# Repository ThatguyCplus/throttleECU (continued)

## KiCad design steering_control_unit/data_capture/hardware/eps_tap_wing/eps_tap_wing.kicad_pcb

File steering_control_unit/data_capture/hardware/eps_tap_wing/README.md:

# EPS tap FeatherWing

A factory-assembled FeatherWing that holds the logger's whole front end, so the build has no loose resistors. It replaces the FeatherWing Proto and every part in section 3 of [BOM.md](../../BOM.md). The circuit is the same apart from the changes listed below.

**Rev 1.5: cheaper to build at JLCPCB**
- Divider values were re-picked from JLCPCB's **Basic** library, which loads with no setup fee; each Extended part type costs about $3. Extended types dropped from 8 to 2: the op-amp and the ADS1115.

  | Channel | Was | Now | Effect |
  |---|---|---|---|
  | VT3, VT6, VCC2 | 1M / 1.8M | 1M / 1M | 5 V → 2.50 V (was 3.21 V); resolution still ~0.016 %/step |
  | +B, X1–X4 | 1M / 150k | 1M / 100k | 36 V full scale (was 25 V); ~9 mV/step |
  | NEP, WLP, RT+, IG1 | 100k / 27k | 100k / 33k | 14.4 V → 3.57 V; still reads high at 9 V |
  | VSP | 100k / 180k | 100k / 100k | 5 V → 2.50 V |
  | Current, Vref | 10k / 18k | 10k / 47k | More of the ADC range used: better resolution |
  | Clamp diodes | BAT54WS | 1N4148WS | Basic part, lower leakage |
  | Op-amps | MCP6024 | MCP6004 | Same pins; about 1/10 the price |
- The BOM now carries a **JLCPCB Part #** column, so the upload matches exactly. The MCP6004 has no part number yet: pick MCP6004-I/ST at upload.
- `firmware/eps_logger/config.h` has a new `CFG_FRONT_END_TAP_WING` switch that sets the divider constants: 1 for this board, 0 for the hand-built Proto Wing.

**Rev 1.4: status LED, 4-layer board**
- **Red status LED** (D6, with R32 1 kΩ) on the **back**, next to the "LED" label. It's wired to Feather pin D13, which the logger firmware already uses for its status codes (`CFG_PIN_LED`), so it mirrors them with no firmware change. The two parts are 0805 so you can hand-solder them; or ask JLC for bottom-side assembly of just those two.
- **Now a 4-layer board.** With rev 1.3's extra parts plus the LED, the 2-layer board was full: the router always left one or two connections. With an inner GND plane and a third routing layer it routes completely, and the signal traces got **thicker (0.3 mm)**.
- Solder jumpers use plain rectangular pads. The rounded custom pads were being exported to the auto-router on the wrong layer.

**Rev 1.3: room to grow**
- **Four spare protected inputs, X1–X4,** for future signals: motor M+/M−, Vcc1, ground shift, or anything else that's a voltage. Each has the same protection as +B: a 1 MΩ series resistor with a bypass jumper, a 100 kΩ divider (0–36 V full scale) and a 1 nF filter. A second quad op-amp (U2) buffers them into an **ADS1115 16-bit ADC** (U3) on I2C at address 0x48.
- **J2 is now a 15-way JST XA** (2.5 mm pitch, positive locking latch). It's the same length as the old 11-way plug and carries the original 11 signals plus X1–X4.
- Passives went from 0603 to 0402 and the op-amps from SOIC-14 to TSSOP-14 to make room. Everything is still factory-assembled on one side.

**Rev 1.2:**
- All wiring is from the **back**: J2, J3 and the bypass jumpers are on the bottom side, and all 42 SMD parts moved to the top (still one-sided assembly).
- The wing is a "bottom Wing" (allowed by the Feather spec): it sits at the bottom of the stack, with the Feather plugged in on top.
- **HINDSIGHT** is on the back silkscreen, together with the terminal labels and "IGN OFF TO PLUG". The revision is on the top.

**Rev 1.1:**
- Follows the [Adafruit Feather specification](https://learn.adafruit.com/adafruit-feather/feather-specification).
- Each series resistor has a bypass solder jumper, so the probe resistors can live on the board or at the probe ends.
- Adds the current sensor's Vref channel on A5.
- The clamp terminal (J3) is now 4-way.

## Feather specification check

| Spec item | This wing |
|-----------|-----------|
| 0.9" × 2.0" board, 0.1" holes at each corner | 22.86 × 50.8 mm, four 2.5 mm holes 2.54 mm in from the edges |
| 16-pin strip on the bottom side, centred 1.0" from the left (USB) edge | Pins 1–16 at x = 6.35–44.45 mm (centre 25.4 mm), y = 21.59 mm |
| 12-pin strip on the top side, 1.2" from the left edge, 0.8" between strips | Pins 17–28 at x = 16.51–44.45 mm (centre 30.48 mm), y = 1.27 mm |
| Wings take 3.3 V from the Feather; at least 100 mA available | The op-amps and ADC draw about 2 mA from 3V3; the clamp draws ≤12 mA from USB |
| AREF, the free pin (right of TX), RX/TX, SPI and its CS: avoid | None of them are used |
| I2C pull-ups belong on Wings | The ADS1115 uses I2C; the Adalogger in the same stack already has the pull-ups |
| Reset button "ideally" on Wings | Not fitted: the OLED FeatherWing on top of the stack has one |
| Wings may be "bottom" Wings with the Feather on top | Used here, so the terminals face out of the back |

The board check script confirms the header pads line up with the Feather footprint every time the board is regenerated.

## Design rules

| Item | Value |
|------|-------|
| Layers | 4: **F.Cu** parts + signals, **In1.Cu** solid GND plane, **In2.Cu** signals + 3V3 + GND fill, **B.Cu** connectors + signals + GND fill |
| Signal traces | 0.3 mm. They carry microamps, so this is for robustness, not current |
| 3V3 / 5V traces | 0.3 mm. The 3V3 traces are short stubs and the USB 5 V carries ≤15 mA; 0.3 mm also fits into the 0.5 mm-pitch ADC pins |
| Status-LED traces | 0.2 mm (about 1.4 mA) |
| Clearance | 0.15 mm |
| Vias | 0.5 mm pad, 0.25 mm drill |

JLCPCB's standard minimum is 0.127 mm, so these widths have plenty of margin. A 4-layer board costs a little more than 2-layer, but it gives a solid ground plane under all the high-impedance inputs, which is better for noise. `make_pcb.py` still builds the 2-layer version if you set `EPS_LAYERS=2`, but with this many parts it won't fully route.

| File | What it is |
|------|------------|
| [eps_tap_wing.kicad_sch](eps_tap_wing.kicad_sch) / [schematic PDF](doc/eps_tap_wing_schematic.pdf) | Schematic. ERC: 0 errors, 0 warnings |
| [eps_tap_wing.kicad_pcb](eps_tap_wing.kicad_pcb) | Board, 50.8 × 22.86 mm (standard FeatherWing), 4 layers, fully routed. DRC: 0 errors, 0 unconnected, matches the schematic |
| [doc/render_top.png](doc/render_top.png), [doc/render_bottom.png](doc/render_bottom.png) | 3D renders |
| [fab/eps_tap_wing_bom_jlc.csv](fab/eps_tap_wing_bom_jlc.csv), [fab/eps_tap_wing_cpl_jlc.csv](fab/eps_tap_wing_cpl_jlc.csv) | Assembly BOM and pick-and-place, in JLCPCB's column format, SMD parts only |
| [gen/](gen/) | Generator scripts. The schematic and board are built from [gen/design.py](gen/design.py) |

## The stack

The tap wing also stacks with the [bench stim wing](../../../bench_stim_wing/README.md), which can power everything from 12 V and drive the EPS inputs. **When the stack runs from 12 V, its ground must go to the ECU end of A4 (PG)**, not chassis: see [STACK_MODES.md](../../STACK_MODES.md) for every combination.

```
  OLED FeatherWing
  Adalogger FeatherWing
  Feather M4 CAN          (its male headers plug down into the wing)
  ─ female headers soldered on the wing's top side ─
  EPS tap wing            (SMD on top, facing the Feather; ~8 mm of header gap is plenty)
  ─ back side: J2 taps, J3 clamp, bypass jumpers, labels ── wire from here
```

The terminals point out of the back of the stack, so the harness never has to pass between boards. Leave room under the stack for the J2 plug and its cable (about 15 mm).

Solder joints you make yourself: the two female header rows on the top (28 joints) and the two connectors on the back (19 joints). Every resistor, capacitor, diode, both op-amps and the ADC arrive already fitted. The status LED and its resistor (0805, on the back) are either 2 more hand-soldered parts or bottom-side assembly.

## Connectors

**J2, EPS taps** (JST XA B15B-XASK-1, 2.5 mm pitch, locking; mating housing XAP-15V-1 with SXA-001T-P0.6 crimp contacts, or buy pre-crimped XA leads). Read the back silkscreen with the board face down: the labels sit under each pin, and pin 1 (VT3) is at the right-hand end.

| J2 pin | Silk | Car pin | On the wing |
|--------|------|---------|-------------|
| 1 | VT3 | B10 | 1 MΩ / 1 MΩ → buffer → A2 |
| 2 | VT6 | B8 | 1 MΩ / 1 MΩ → buffer → A3 |
| 3 | VCC2 | B2 | 1 MΩ / 1 MΩ → buffer → A0 |
| 4 | GND | B9 (T/S GND) | 100 Ω → logger GND, the only ground reference |
| 5 | SHLD | cable shield | logger GND; don't connect the shield at the car end |
| 6 | +B | A2 | 1 MΩ / 100 kΩ → buffer → A1 |
| 7 | IG1 | B6 | 100 kΩ / 33 kΩ → D12 |
| 8 | RT+ | B11 | 100 kΩ / 33 kΩ → D11 (optional: leave it empty and it reads "off") |
| 9 | WLP | B13 | 100 kΩ / 33 kΩ → D9 |
| 10 | NEP | B14 | 100 kΩ / 33 kΩ → D6 |
| 11 | VSP | B4 | 100 kΩ / 100 kΩ → D5 |
| 12–15 | X1–X4 | spare | 1 MΩ / 100 kΩ → U2 buffer → ADS1115 AIN0–AIN3 |

The torque-sensor lines sit at one end, behind GND and SHLD, so a stray strand can't put +B onto them. +B's other neighbour is IG1, which is also battery level. The digital lines follow the Feather's pin order, so their tracks don't cross. Crimp every contact properly and check each wire with a tug.

**J3, current clamp** (Phoenix MPT 0,5/4-2,54 fixed screw terminal, 2.54 mm pitch). A 3.5 mm plug-in 4-way terminal would sit over the Feather-spec corner mounting holes. The clamp has its own flying leads anyway. Pin 1 is the one nearest the 16-pin header edge, marked with a triangle.

| J3 pin | HSTS016L wire |
|--------|---------------|
| 1 | red: +5 V (from the Feather USB pin, i.e. the power bank) |
| 2 | black: 0 V, plus the sensor cable's shield |
| 3 | yellow: OUT → 10 k / 47 k / 100 nF → A4 |
| 4 | white: Vref → 10 k / 47 k / 100 nF → A5 (current = Vout − Vref, which cancels the sensor's reference drift) |

## Probe resistors: on the board or at the probe

Each car-facing series resistor has a **solder jumper** across it. The jumpers are the row of pads under J2 on the back, one under each terminal, and they ship **open**.

| Where you want the resistors | What to do |
|------------------------------|------------|
| **On the board** (default) | Nothing. Leave the jumpers open. Protect the cable as described below |
| **At the probe ends** (whole cable protected, as in [PROTO_BUILD.md](../../PROTO_BUILD.md)) | Bridge each jumper with a blob of solder. Then fit 1 MΩ (VT3, VT6, VCC2, +B, X1–X4), 100 kΩ (VSP, NEP, WLP, RT+, IG1) and 100 Ω (GND) inline at the probes |

| Jumper | Bypasses | J2 terminal |
|--------|----------|-------------|
| JP1 | R3 (1 MΩ) | VT3 |
| JP2 | R5 (1 MΩ) | VT6 |
| JP3 | R1 (1 MΩ) | VCC2 |
| JP4 | R11 (100 Ω) | GND |
| JP5 | R7 (1 MΩ) | +B |
| JP6–JP10 | R20, R18, R16, R14, R12 (100 kΩ) | IG1, RT+, WLP, NEP, VSP |
| JP11–JP14 | R24, R26, R28, R30 (1 MΩ) | X1–X4 |

Never bridge a jumper without fitting its probe resistor: that connects the car straight to the dividers.

The pin map is the one `firmware/eps_logger/config.h` already uses, so the firmware needs no changes for the original signals.

## Spare inputs X1–X4

| Signal type | Change on the board |
|-------------|---------------------|
| Up to 36 V (battery-level, motor terminals) | None: 1 MΩ / 100 kΩ gives 0–3.27 V at the ADC |
| 0–5 V sensor | Swap the 100 kΩ (R25, R27, R29, R31) for 1 MΩ: 5 V → 2.50 V, same as VT3 |

The ADS1115 reads all four channels at about 200 samples per second each, with a programmable gain (±0.256 V to ±4.096 V). That suits slow-to-medium signals; anything that must line up sample-for-sample with torque belongs on the Feather's own ADC. The firmware doesn't read U3 yet.

## Safety: the one trade-off

With the probe resistors on the wing, the cable between the car and the wing is no longer behind them. A cable fault, such as a crushed jacket or a strand bridging two terminals, now reaches the EPS directly instead of through ≥100 kΩ. To make up for that:

- Use one sheathed multicore cable (12-core shielded, as in BOM.md §5). Strap it down so it can't chafe, and keep it away from the pedal box and seat rails.
- Crimp ferrules on every wire and heat-shrink each back-probe pin.
- Fit the plug and probes with the **ignition OFF** (this is printed on the board). Continuity-check neighbouring probes before key-on, as in BOM.md's worst-case table.
- Run the firmware's `c` lead check with the engine off, then running.

Faults on the logger side of the terminals are covered just as in BOM.md: everything after J2 is ≥100 kΩ (1 MΩ on the torque lines) from the car.

## Changes from the BOM.md front end

| BOM.md part | Wing part | Why |
|-------------|-----------|-----|
| MCP6024-I/P (DIP-14) | MCP6004-I/ST (TSSOP-14) | Same pinout and rail-to-rail, 1 pA inputs; 1 MHz instead of 10 MHz (plenty) for about a tenth of the price |
| BAT85 (DO-35) | 1N4148WS (SOD-323) | JLC Basic part, same 3V3 clamp role; 25 nA leakage can't disturb the dividers |
| 2 × 6-way screw terminal | 15-way locking JST XA + 4-way screw terminal | Unplug the car harness in one go; 4 spare positions |
| — | X1–X4 inputs, second quad op-amp, ADS1115 | Room for future signals |
| — | 10 k / 47 k / 100 nF on the clamp's Vref → A5 | Cancels the current sensor's reference drift (needs a firmware update to use, see below) |
| — | 14 bypass solder jumpers | Choose between probe resistors on the board or at the probes |

All resistors are 0402 1 % parts and all capacitors are 0402 X7R (JLC Basic).

## Rebuilding the design

All scripts run with KiCad 10's bundled Python, from `gen/`:

```bash
"/c/Program Files/KiCad/10.0/bin/python.exe" make_sch.py
"/c/Program Files/KiCad/10.0/bin/kicad-cli.exe" sch export netlist -o ../eps_tap_wing.net ../eps_tap_wing.kicad_sch
sh route.sh
```

`route.sh` runs four steps:
1. `make_pcb.py place` places the parts and exports a Specctra DSN.
2. Freerouting routes the board.
3. `make_pcb.py finish` imports the routes and pours GND on both layers.
4. DRC with schematic parity runs, then `export_fab.py` writes the Gerbers, drill files, BOM and CPL.

Change the circuit or the placement in `design.py` and re-run. Hand-editing in KiCad is also fine, but then stop running the generators, because they would overwrite your edits.

## What's left

1. **Gerbers are ready** in `fab/eps_tap_wing_gerbers.zip`, with the assembly BOM and CPL next to them. **Nothing has been ordered or published.**
2. Before ordering:
   - Check the JLC CPL rotations in their viewer. Bottom-side parts are where offsets usually need a tweak.
   - Match each MPN to an in-stock LCSC part.
3. **Firmware:** `eps_logger` doesn't read A5 or the ADS1115 yet.
   - To use the Vref channel, compute current as A4 − A5 instead of A4 minus the key-on zero.
   - Reading X1–X4 means polling U3 over I2C (0x48) a few hundred times a second.
   - Both need new fields in the log record.

Routing used Freerouting 2.2.0 on a downloaded Temurin JRE 25 (not installed system-wide). To re-route: `JAVA=<path to java 25> sh gen/route.sh`. Freerouting results vary from run to run, so re-run it if a connection is left over.

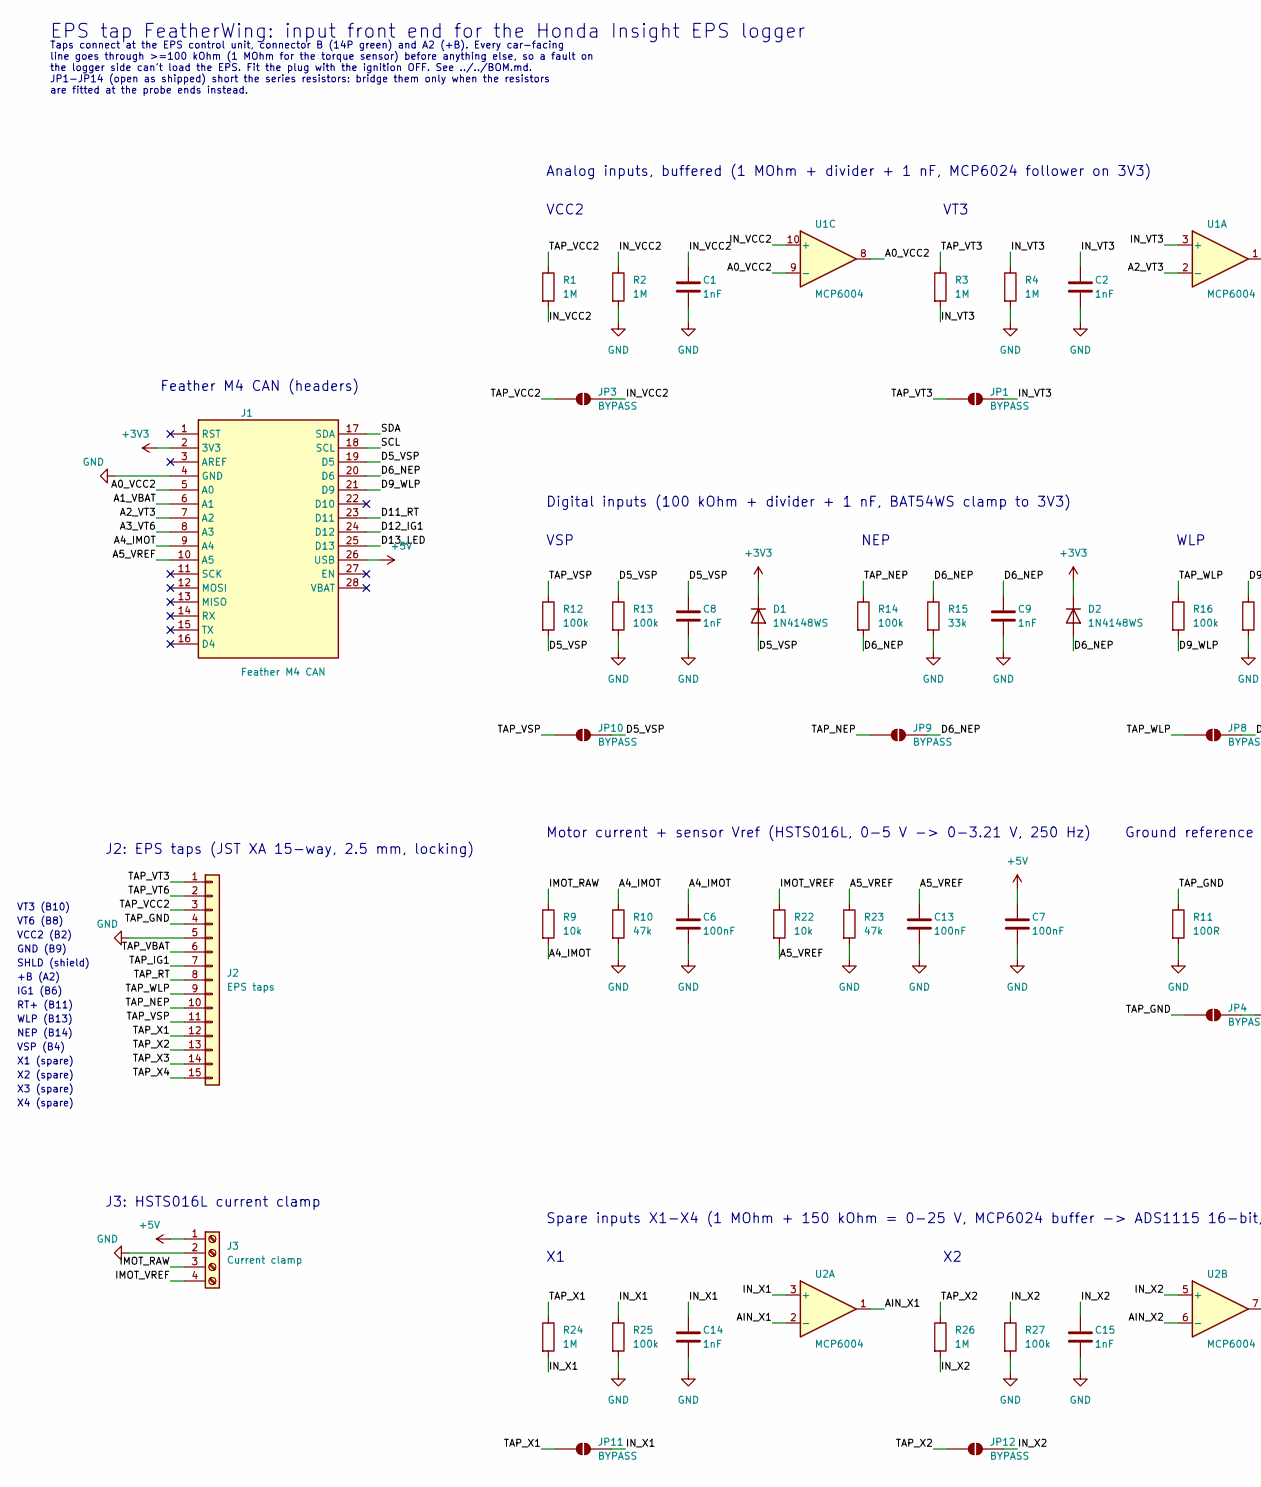
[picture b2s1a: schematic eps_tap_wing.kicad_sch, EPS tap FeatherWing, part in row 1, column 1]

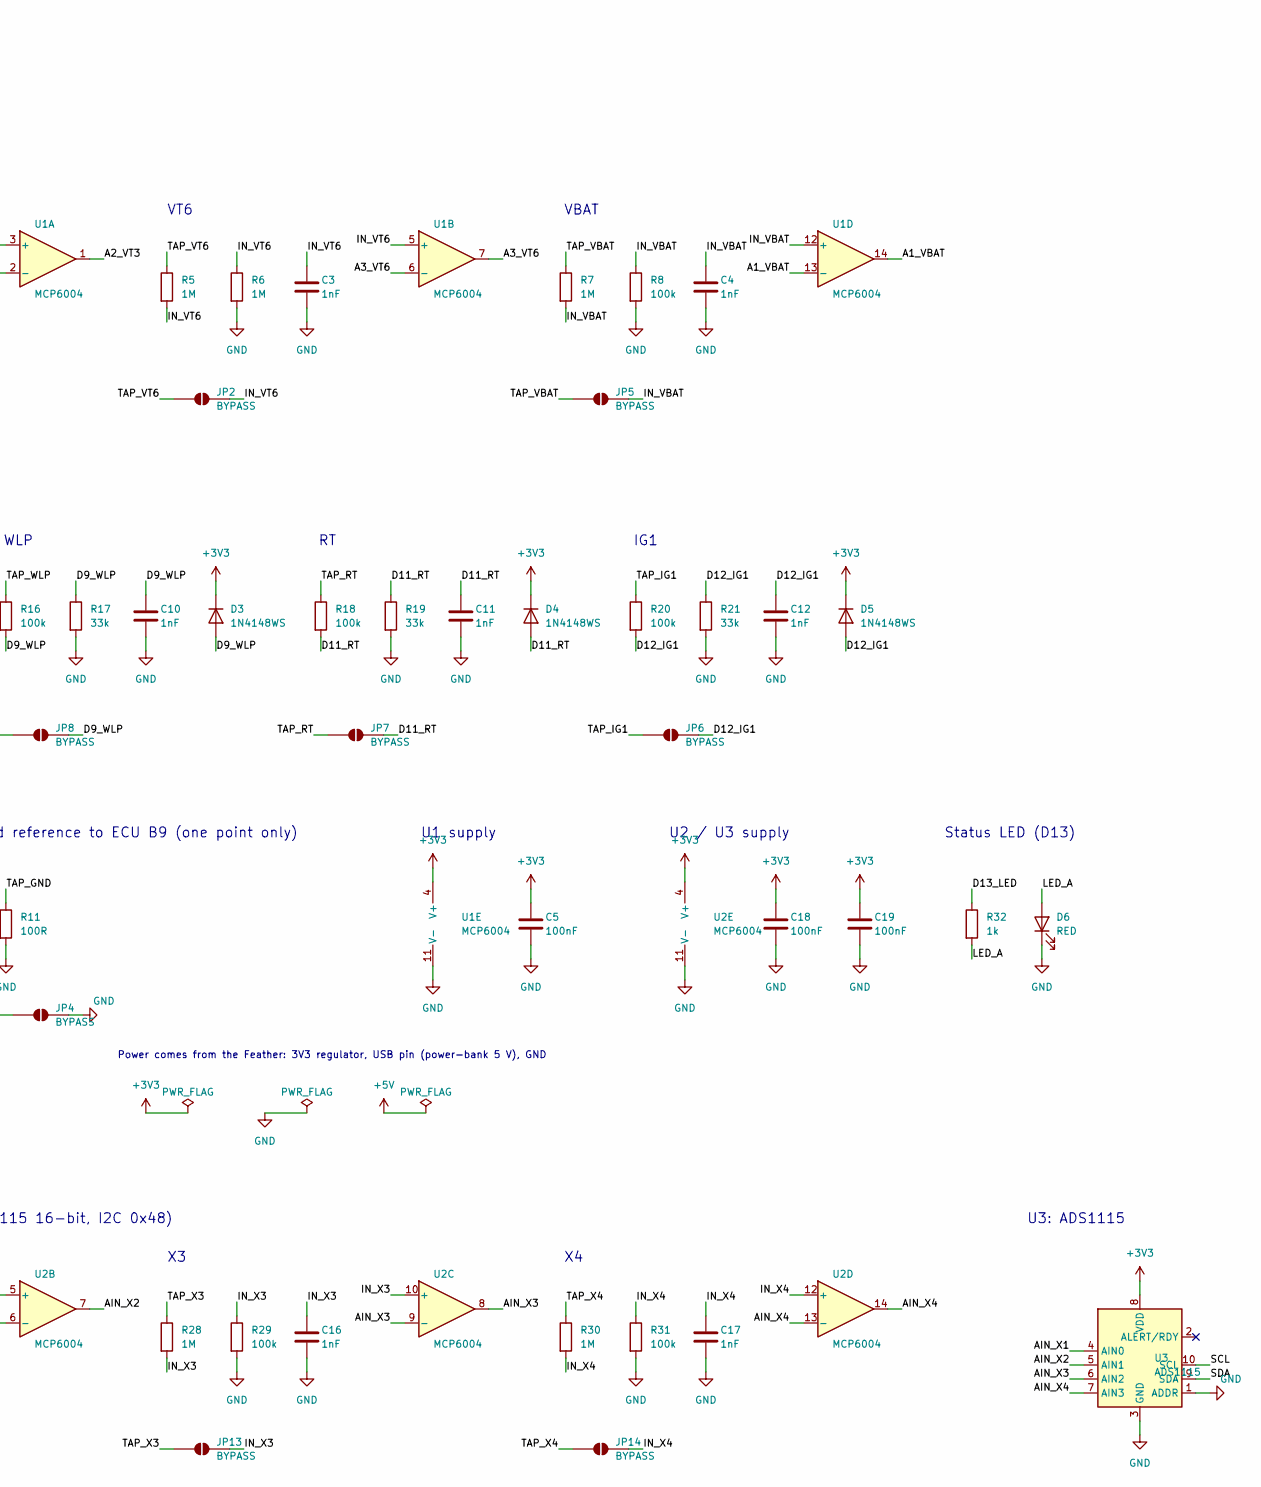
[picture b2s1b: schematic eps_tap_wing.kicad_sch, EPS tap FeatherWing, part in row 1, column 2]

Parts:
C1, C2, C3, C4, C8, C9, C10, C11, C12, C14, C15, C16, C17: 1nF; C_0402_1005Metric; MPN 0402B102K500NT; LCSC C1523
C5, C6, C7, C13, C18, C19: 100nF; C_0402_1005Metric; MPN CL05B104KO5NNNC; LCSC C1525
D1, D2, D3, D4, D5: 1N4148WS; D_SOD-323; MPN 1N4148WS; LCSC C2128
D6: RED; LED_0805_2012Metric_Pad1.15x1.40mm_HandSolder; MPN NCD0805R1; LCSC C84256
J1: Feather M4 CAN; Feather_Wing_Headers
J2: EPS taps; JST_XA_B15B-XASK-1_1x15_P2.50mm_Vertical; MPN JST B15B-XASK-1 + XAP-15V-1 housing, SX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
J3: Current clamp; TerminalBlock_Phoenix_MPT-0,5-4-2.54_1x04_P2.54mm_Horizontal; MPN Phoenix MPT 0,5/4-2,54 (1725672)
JP1, JP2, JP3, JP4, JP5, JP6, JP7, JP8, JP9, JP10, JP11, JP12, JP13, JP14: BYPASS; SolderJumper_Bypass
R1, R2, R3, R4, R5, R6, R7, R24, R26, R28, R30: 1M; R_0402_1005Metric; MPN 0402WGF1004TCE; LCSC C26083
R8, R12, R13, R14, R16, R18, R20, R25, R27, R29, R31: 100k; R_0402_1005Metric; MPN 0402WGF1003TCE; LCSC C25741
R9, R22: 10k; R_0402_1005Metric; MPN 0402WGF1002TCE; LCSC C25744
R10, R23: 47k; R_0402_1005Metric; MPN 0402WGF4702TCE; LCSC C25792
R11: 100R; R_0402_1005Metric; MPN 0402WGF1000TCE; LCSC C25076
R15, R17, R19, R21: 33k; R_0402_1005Metric; MPN 0402WGF3302TCE; LCSC C25779
R32: 1k; R_0805_2012Metric_Pad1.20x1.40mm_HandSolder; MPN 0805W8F1001T5E; LCSC C17513
U1, U2: MCP6004; TSSOP-14_4.4x5mm_P0.65mm; MPN MCP6004-I/ST
U3: ADS1115; TSSOP-10_3x3mm_P0.5mm; MPN ADS1115IDGSR; LCSC C37593

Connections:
+3V3: C5.1, C18.1, C19.1, D1.1 (K), D2.1 (K), D3.1 (K), D4.1 (K), D5.1 (K), J1.2 (3V3), U1.4 (V+), U2.4 (V+), U3.8 (VDD)
+5V: C7.1, J1.26 (USB), J3.1
/A0_VCC2: J1.5 (A0), U1.8, U1.9 (-)
/A1_VBAT: J1.6 (A1), U1.13 (-), U1.14
/A2_VT3: J1.7 (A2), U1.1, U1.2 (-)
/A3_VT6: J1.8 (A3), U1.6 (-), U1.7
/A4_IMOT: C6.1, J1.9 (A4), R9.2, R10.1
/A5_VREF: C13.1, J1.10 (A5), R22.2, R23.1
/AIN_X1: U2.1, U2.2 (-), U3.4 (AIN0)
/AIN_X2: U2.6 (-), U2.7, U3.5 (AIN1)
/AIN_X3: U2.8, U2.9 (-), U3.6 (AIN2)
/AIN_X4: U2.13 (-), U2.14, U3.7 (AIN3)
/D5_VSP: C8.1, D1.2 (A), J1.19 (D5), JP10.2 (B), R12.2, R13.1
/D6_NEP: C9.1, D2.2 (A), J1.20 (D6), JP9.2 (B), R14.2, R15.1
/D9_WLP: C10.1, D3.2 (A), J1.21 (D9), JP8.2 (B), R16.2, R17.1
/D11_RT: C11.1, D4.2 (A), J1.23 (D11), JP7.2 (B), R18.2, R19.1
/D12_IG1: C12.1, D5.2 (A), J1.24 (D12), JP6.2 (B), R20.2, R21.1
/D13_LED: J1.25 (D13), R32.1
/IMOT_RAW: J3.3, R9.1
/IMOT_VREF: J3.4, R22.1
/IN_VBAT: C4.1, JP5.2 (B), R7.2, R8.1, U1.12 (+)
/IN_VCC2: C1.1, JP3.2 (B), R1.2, R2.1, U1.10 (+)
/IN_VT3: C2.1, JP1.2 (B), R3.2, R4.1, U1.3 (+)
/IN_VT6: C3.1, JP2.2 (B), R5.2, R6.1, U1.5 (+)
/IN_X1: C14.1, JP11.2 (B), R24.2, R25.1, U2.3 (+)
/IN_X2: C15.1, JP12.2 (B), R26.2, R27.1, U2.5 (+)
/IN_X3: C16.1, JP13.2 (B), R28.2, R29.1, U2.10 (+)
/IN_X4: C17.1, JP14.2 (B), R30.2, R31.1, U2.12 (+)
/LED_A: D6.2 (A), R32.2
/SCL: J1.18 (SCL), U3.10 (SCL)
/SDA: J1.17 (SDA), U3.9 (SDA)
/TAP_GND: J2.4, JP4.1 (A), R11.1
/TAP_IG1: J2.7, JP6.1 (A), R20.1
/TAP_NEP: J2.10, JP9.1 (A), R14.1
/TAP_RT: J2.8, JP7.1 (A), R18.1
/TAP_VBAT: J2.6, JP5.1 (A), R7.1
/TAP_VCC2: J2.3, JP3.1 (A), R1.1
/TAP_VSP: J2.11, JP10.1 (A), R12.1
/TAP_VT3: J2.1, JP1.1 (A), R3.1
/TAP_VT6: J2.2, JP2.1 (A), R5.1
/TAP_WLP: J2.9, JP8.1 (A), R16.1
/TAP_X1: J2.12, JP11.1 (A), R24.1
/TAP_X2: J2.13, JP12.1 (A), R26.1
/TAP_X3: J2.14, JP13.1 (A), R28.1
/TAP_X4: J2.15, JP14.1 (A), R30.1
GND: C1.2, C2.2, C3.2, C4.2, C5.2, C6.2, C7.2, C8.2, C9.2, C10.2, C11.2, C12.2, C13.2, C14.2, C15.2, C16.2, C17.2, C18.2, C19.2, D6.1 (K), J1.4 (GND), J2.5, J3.2, JP4.2 (B), R2.2, R4.2, R6.2, R8.2, R10.2, R11.2, R13.2, R15.2, R17.2, R19.2, R21.2, R23.2, R25.2, R27.2, R29.2, R31.2, U1.11 (V-), U2.11 (V-), U3.1 (ADDR), U3.3 (GND)

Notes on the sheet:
EPS tap FeatherWing: input front end for the Honda Insight EPS logger
Taps connect at the EPS control unit, connector B (14P green) and A2 (+B). Every car-facing line goes through >=100 kOhm (1 MOhm for the torque sensor) before anything else, so a fault on the logger side can't load the EPS. Fit the plug with the ignition OFF. See ../../BOM.md. JP1-JP14 (open as shi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
Feather M4 CAN (headers)
J2: EPS taps (JST XA 15-way, 2.5 mm, locking)
VT3 (B10)
VT6 (B8)
VCC2 (B2)
GND (B9)
SHLD (shield)
+B (A2)
IG1 (B6)
RT+ (B11)
WLP (B13)
NEP (B14)
VSP (B4)
X1 (spare)
X2 (spare)
X3 (spare)
X4 (spare)
J3: HSTS016L current clamp
Analog inputs, buffered (1 MOhm + divider + 1 nF, MCP6024 follower on 3V3)
VCC2
VT3
VT6
VBAT
Digital inputs (100 kOhm + divider + 1 nF, BAT54WS clamp to 3V3)
VSP
NEP
WLP
IG1
Motor current + sensor Vref (HSTS016L, 0-5 V -> 0-3.21 V, 250 Hz)
Ground reference to ECU B9 (one point only)
U1 supply
U2 / U3 supply
Status LED (D13)
Spare inputs X1-X4 (1 MOhm + 150 kOhm = 0-25 V, MCP6024 buffer -> ADS1115 16-bit, I2C 0x48)
U3: ADS1115
Power comes from the Feather: 3V3 regulator, USB pin (power-bank 5 V), GND

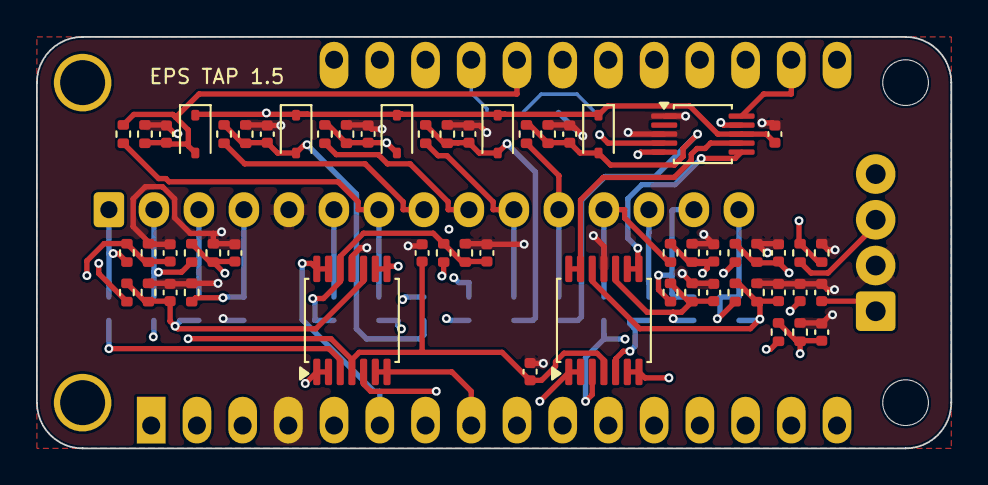
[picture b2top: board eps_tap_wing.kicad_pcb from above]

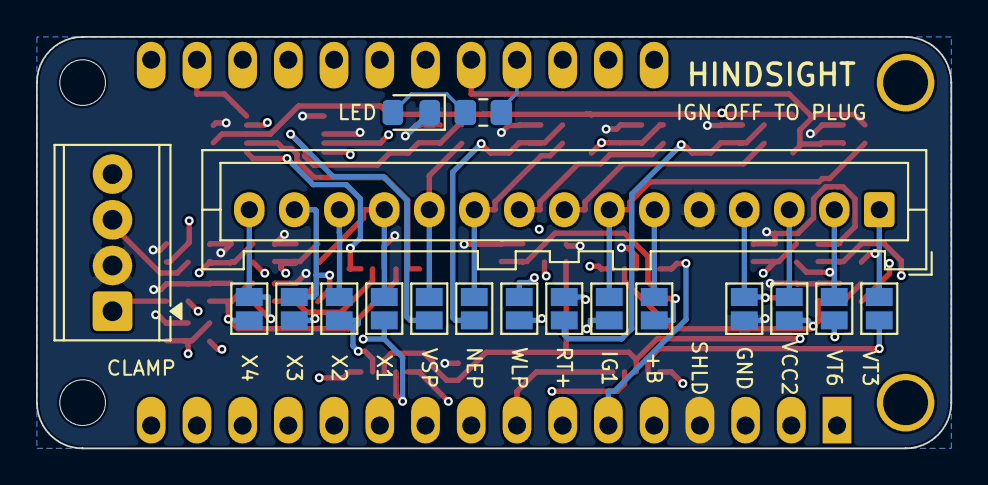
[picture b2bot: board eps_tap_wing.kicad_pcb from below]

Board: 4 copper layers, 50.8 x 22.9 mm, 77 parts (18 on the bottom side), 46 nets.

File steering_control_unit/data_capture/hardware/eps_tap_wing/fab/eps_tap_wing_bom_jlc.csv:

Comment,Designator,Footprint,Manufacturer Part,JLCPCB Part #,Quantity
1nF,"C1,C2,C3,C4,C8,C9,C10,C11,C12,C14,C15,C16,C17",C_0402_1005Metric,0402B102K500NT,C1523,13
100nF,"C5,C6,C7,C13,C18,C19",C_0402_1005Metric,CL05B104KO5NNNC,C1525,6
1N4148WS,"D1,D2,D3,D4,D5",D_SOD-323,1N4148WS,C2128,5
1M,"R1,R2,R3,R4,R5,R6,R7,R24,R26,R28,R30",R_0402_1005Metric,0402WGF1004TCE,C26083,11
100k,"R8,R12,R13,R14,R16,R18,R20,R25,R27,R29,R31",R_0402_1005Metric,0402WGF1003TCE,C25741,11
10k,"R9,R22",R_0402_1005Metric,0402WGF1002TCE,C25744,2
47k,"R10,R23",R_0402_1005Metric,0402WGF4702TCE,C25792,2
100R,R11,R_0402_1005Metric,0402WGF1000TCE,C25076,1
33k,"R15,R17,R19,R21",R_0402_1005Metric,0402WGF3302TCE,C25779,4
MCP6004,"U1,U2",TSSOP-14_4.4x5mm_P0.65mm,MCP6004-I/ST,,2
ADS1115,U3,TSSOP-10_3x3mm_P0.5mm,ADS1115IDGSR,C37593,1
